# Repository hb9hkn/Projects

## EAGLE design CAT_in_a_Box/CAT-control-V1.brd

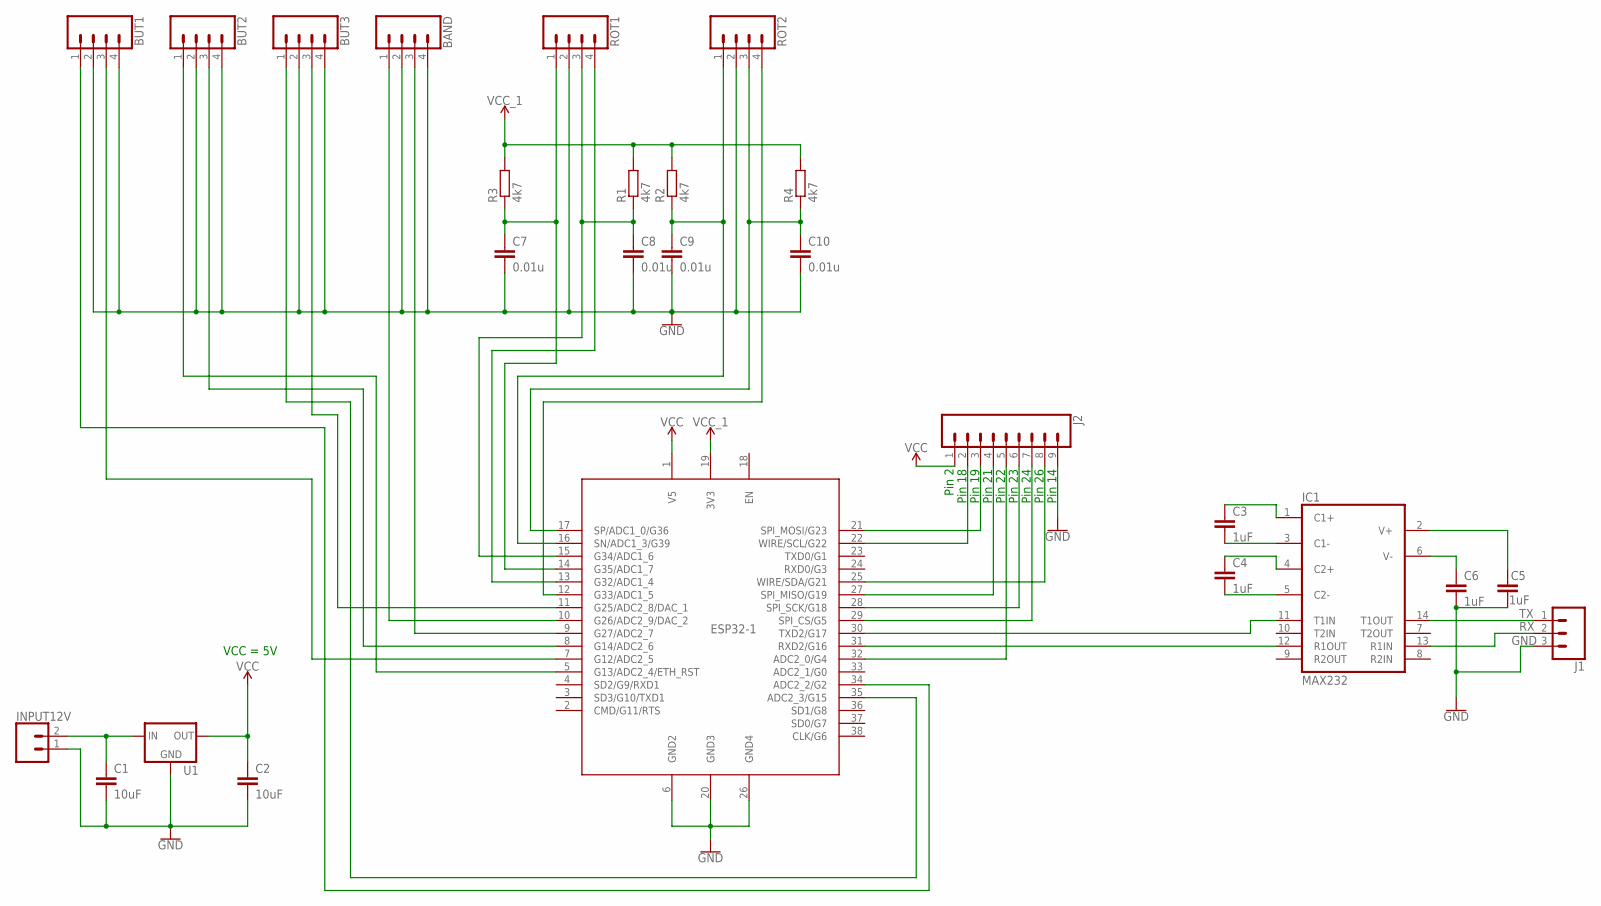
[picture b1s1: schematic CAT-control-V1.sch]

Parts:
BAND: CONN_04POLAR; MOLEX-1X4
BUT1, BUT2, BUT3: CONN_04POLAR; MOLEX-1X4
C1, C2: 10uF; C1206
C3, C4, C5, C6: 1uF; C1206
C7, C8, C9, C10: 0.01u; C025-024X044
ESP32-1: NODEMCU_ESP32_WROOM_32; NODEMCU_ESP32_WROOM_32--38PINS
IC1: MAX232; DIL16
INPUT12V: CONN_025MM; SCREWTERMINAL-5MM-2
J1: CONN_03SCREW; SCREWTERMINAL-3.5MM-3
J2: CONN_09; 1X09
R1, R2, R3, R4: 4k7; R1206
ROT1, ROT2: CONN_04POLAR; MOLEX-1X4
U1: V_REG_78XXSINK; TO220-IGO

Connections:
CMD/G11/RTS: ESP32-1.2 (CMD/G11/RTS)
GND: BAND.2, BAND.4, BUT1.2, BUT1.4, BUT2.2, BUT2.4, BUT3.2, BUT3.4, C1.2, C2.2, C5.1, C6.2, C7.2, C8.2, C9.2, C10.2, ESP32-1.6 (GND2), ESP32-1.20 (GND3), ESP32-1.26 (GND4), IC1.15 (GND), INPUT12V.1, J1.3, J2.9, ROT1.2, ROT2.2, U1.GND
unnamed: C1.1, INPUT12V.2, U1.IN
unnamed: C3.1, IC1.1 (C1+)
unnamed: C3.2, IC1.3 (C1-)
unnamed: C4.1, IC1.4 (C2+)
unnamed: C4.2, IC1.5 (C2-)
unnamed: C8.1, ESP32-1.15 (G34/ADC1_6), R1.1, ROT1.3
unnamed: C6.1, IC1.6 (V-)
unnamed: C5.2, IC1.2 (V+)
unnamed: ESP32-1.31 (RXD2/G16), IC1.12 (R1OUT)
unnamed: ESP32-1.22 (WIRE/SCL/G22), J2.2
unnamed: ESP32-1.21 (SPI_MOSI/G23), J2.3
unnamed: ESP32-1.32 (ADC2_0/G4), J2.5
unnamed: ESP32-1.27 (SPI_MISO/G19), J2.4
unnamed: ESP32-1.29 (SPI_CS/G5), J2.7
unnamed: ESP32-1.28 (SPI_SCK/G18), J2.6
unnamed: ESP32-1.25 (WIRE/SDA/G21), J2.8
unnamed: ESP32-1.13 (G32/ADC1_4), ROT1.4
unnamed: C10.1, ESP32-1.17 (SP/ADC1_0/G36), R4.1, ROT2.3
unnamed: C9.1, ESP32-1.16 (SN/ADC1_3/G39), R2.1, ROT2.1
unnamed: ESP32-1.30 (TXD2/G17), IC1.11 (T1IN)
unnamed: BAND.1, ESP32-1.10 (G26/ADC2_9/DAC_2)
unnamed: ESP32-1.12 (G33/ADC1_5), ROT2.4
unnamed: C7.1, ESP32-1.14 (G35/ADC1_7), R3.1, ROT1.1
unnamed: BAND.3, ESP32-1.9 (G27/ADC2_7)
unnamed: BUT2.1, ESP32-1.5 (G13/ADC2_4/ETH_RST)
unnamed: BUT1.3, ESP32-1.7 (G12/ADC2_5)
unnamed: BUT3.1, ESP32-1.35 (ADC2_3/G15)
unnamed: BUT3.3, ESP32-1.11 (G25/ADC2_8/DAC_1)
unnamed: BUT1.1, ESP32-1.34 (ADC2_2/G2)
unnamed: BUT2.3, ESP32-1.8 (G14/ADC2_6)
RX: IC1.13 (R1IN), J1.2
TX: IC1.14 (T1OUT), J1.1
VCC: C2.1, ESP32-1.1 (V5), IC1.16 (VCC), J2.1, U1.OUT
VCC_1: ESP32-1.19 (3V3), R1.2, R2.2, R3.2, R4.2

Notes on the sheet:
VCC = 5V
Pin 2
Pin 14
Pin 18
Pin 19
Pin 22
Pin 21
Pin 24
Pin 23
Pin 26

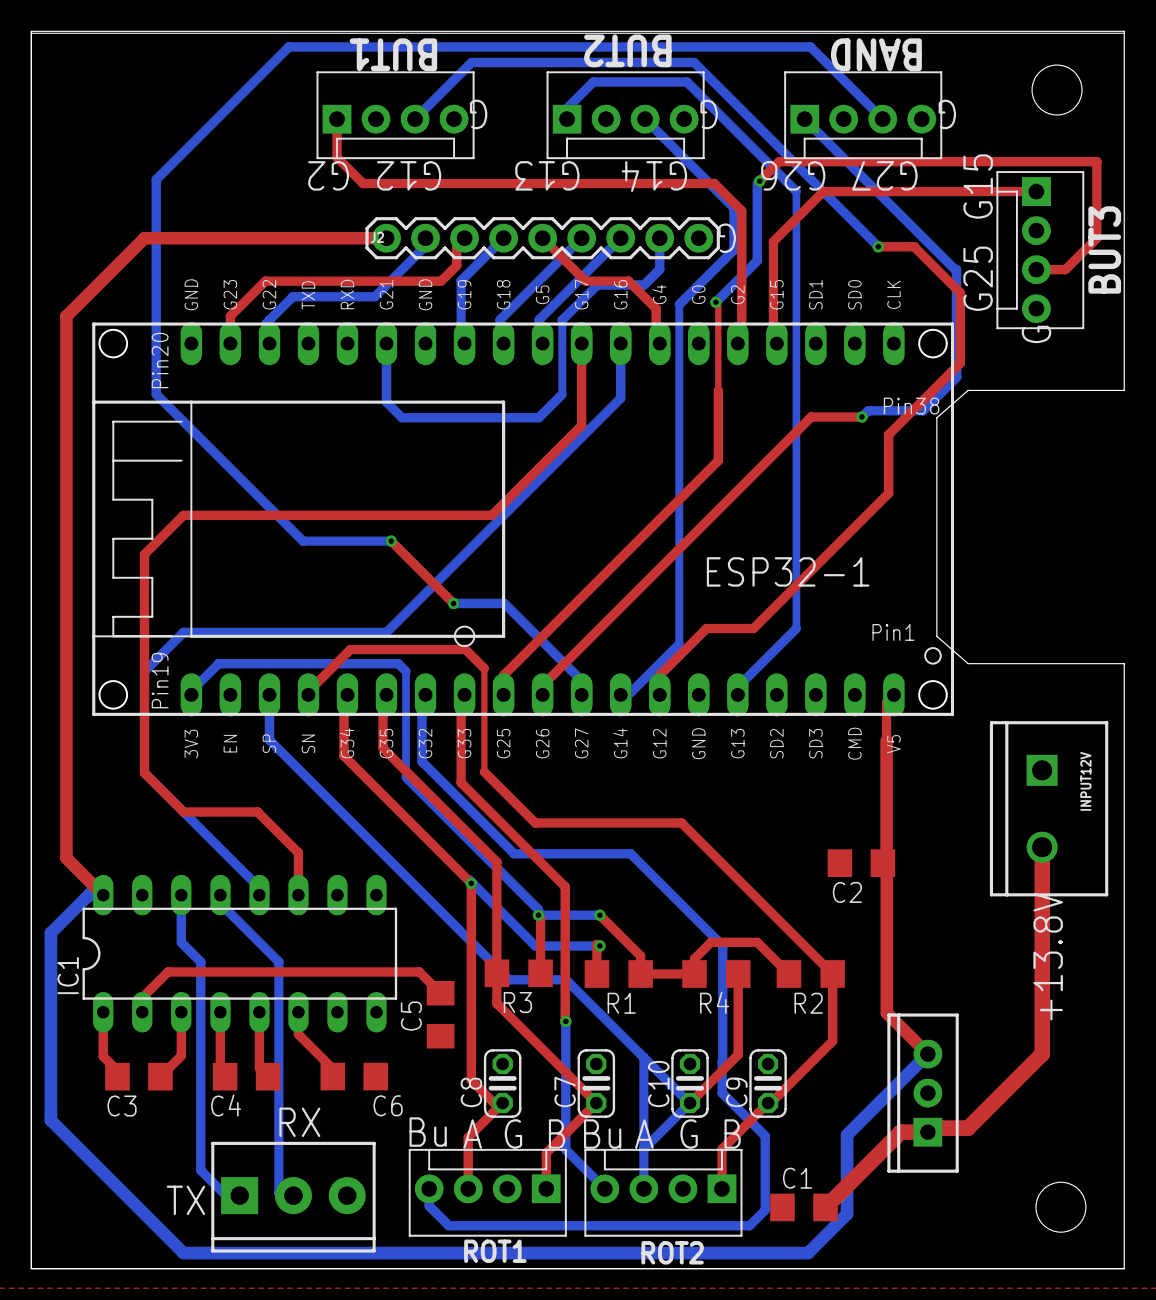
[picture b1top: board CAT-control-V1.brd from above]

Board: 2 copper layers, 71.1 x 80.5 mm, 26 parts (0 on the bottom side), 35 nets.

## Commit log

2025-03-16 Name update

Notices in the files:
parts and their libraries:
SparkFun-Connectors: Licensing: Creative Commons ShareAlike 4.0 International - https://creativecommons.org/licenses/by-sa/4.0
